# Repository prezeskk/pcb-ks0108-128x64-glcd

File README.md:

# KS0108 128x64 Graphic LCD - 2-wire shift register backpack - v1.0 #

## Schematic ##

## Design Rules ##

* Clearance: 8 mil
* Track Width: 20 mil
* Via Diameter: 27 mil
* Via Drill: 13 mil
* Zone Clearance: 8 mil
* Zone Min Width: 8 mil
* Zone Thermal Antipad Clearance: 8 mil
* Zone Thermal Spoke Width: 15 mil

## PCB available on OSH Park ##

* 1.80" x 0.50" (45.82 mm x 12.80 mm)
* $1.50 each ($4.50 for 3)
* [https://oshpark.com/shared_projects/MtvXj55o](https://oshpark.com/shared_projects/MtvXj55o)

### PCB Front ###

### PCB Back ###

### Soldered Front ###

### Soldered Back ###

### Working Front ###

### Working Back ###

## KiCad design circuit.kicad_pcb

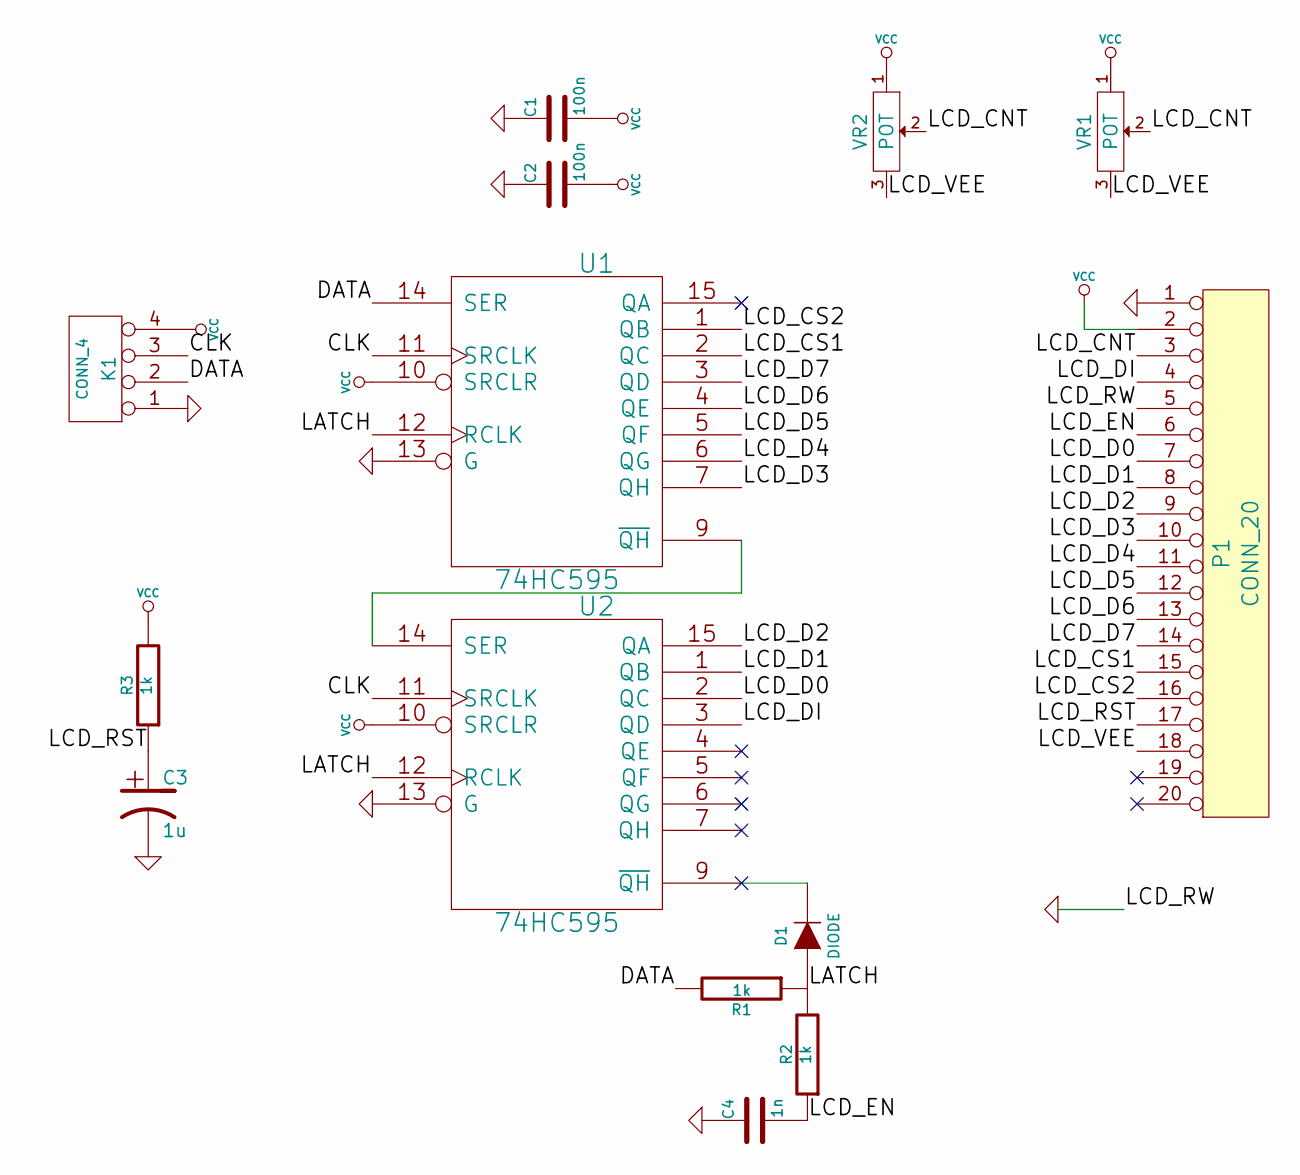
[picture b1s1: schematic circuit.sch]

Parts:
C1, C2: 100n
C3: 1u
C4: 1n
D1: DIODE
K1: CONN_4
P1: CONN_20
R1, R2, R3: 1k
U1, U2: 74HC595
VR1, VR2: POT

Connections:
/CLK: K1.3, U1.11 (SRCLK), U2.11 (SRCLK)
/DATA: K1.2, R1.2, U1.14 (SER)
/LATCH: D1.1 (A), R1.1, R2.2, U1.12 (RCLK), U2.12 (RCLK)
/LCD_CNT: P1.3, VR1.2, VR2.2
/LCD_CS1: P1.15, U1.2 (QC)
/LCD_CS2: P1.16, U1.1 (QB)
/LCD_D0: P1.7, U2.2 (QC)
/LCD_D1: P1.8, U2.1 (QB)
/LCD_D2: P1.9, U2.15 (QA)
/LCD_D3: P1.10, U1.7 (QH)
/LCD_D4: P1.11, U1.6 (QG)
/LCD_D5: P1.12, U1.5 (QF)
/LCD_D6: P1.13, U1.4 (QE)
/LCD_D7: P1.14, U1.3 (QD)
/LCD_DI: P1.4, U2.3 (QD)
/LCD_EN: C4.2, P1.6, R2.1
/LCD_RST: C3.1, P1.17, R3.1
/LCD_VEE: P1.18, VR1.3, VR2.3
GND: C1.1, C2.1, C3.2, C4.1, K1.1, P1.1, P1.5, U1.8 (GND), U1.13 (G), U2.8 (GND), U2.13 (G)
unnamed: U1.9 (~QH), U2.14 (SER)
unnamed: D1.2 (K), U2.9 (~QH)
VCC: C1.2, C2.2, K1.4, P1.2, R3.2, U1.10 (SRCLR), U1.16 (VCC), U2.10 (SRCLR), U2.16 (VCC), VR1.1, VR2.1

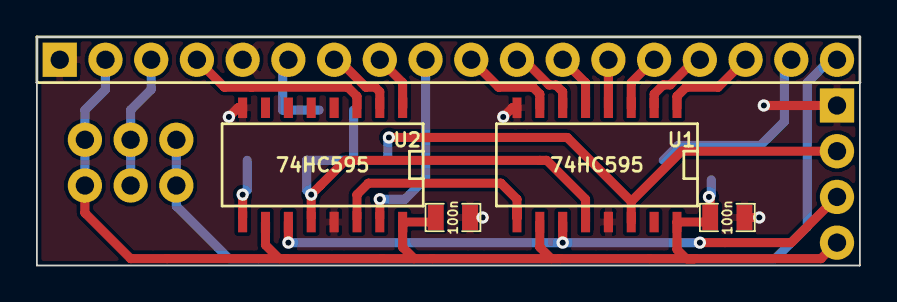
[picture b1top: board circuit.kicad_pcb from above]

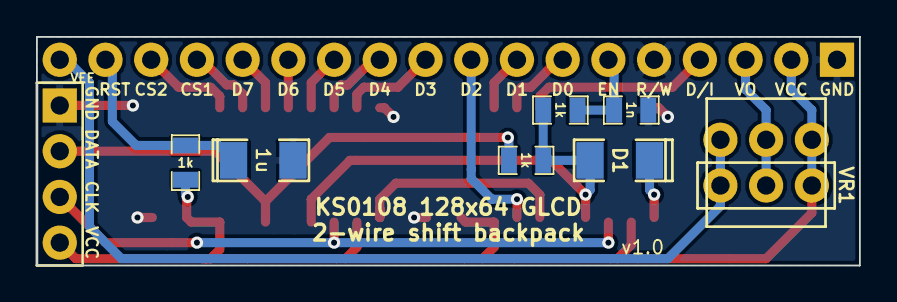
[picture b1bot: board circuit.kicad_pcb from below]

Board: 2 copper layers, 45.7 x 12.7 mm, 14 parts (9 on the bottom side), 22 nets.

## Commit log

2016-02-19 Initial Commit (.gitignore)
2016-02-19 Initial Working Version (v1.0)
2016-02-19 Add OSHPARK.md
2016-02-19 Fix gerber output directory
2016-02-19 Add 'Soldered' and 'Working' pictures to README.md
2016-02-19 Swap PCB-Back <--> PCB-Front
2016-02-19 Rotate Soldered-Back.jpg
